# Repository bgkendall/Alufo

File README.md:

# Alufo

Small split keyboard using stacked one-layer aluminium core boards with an on-board CH552T controller.

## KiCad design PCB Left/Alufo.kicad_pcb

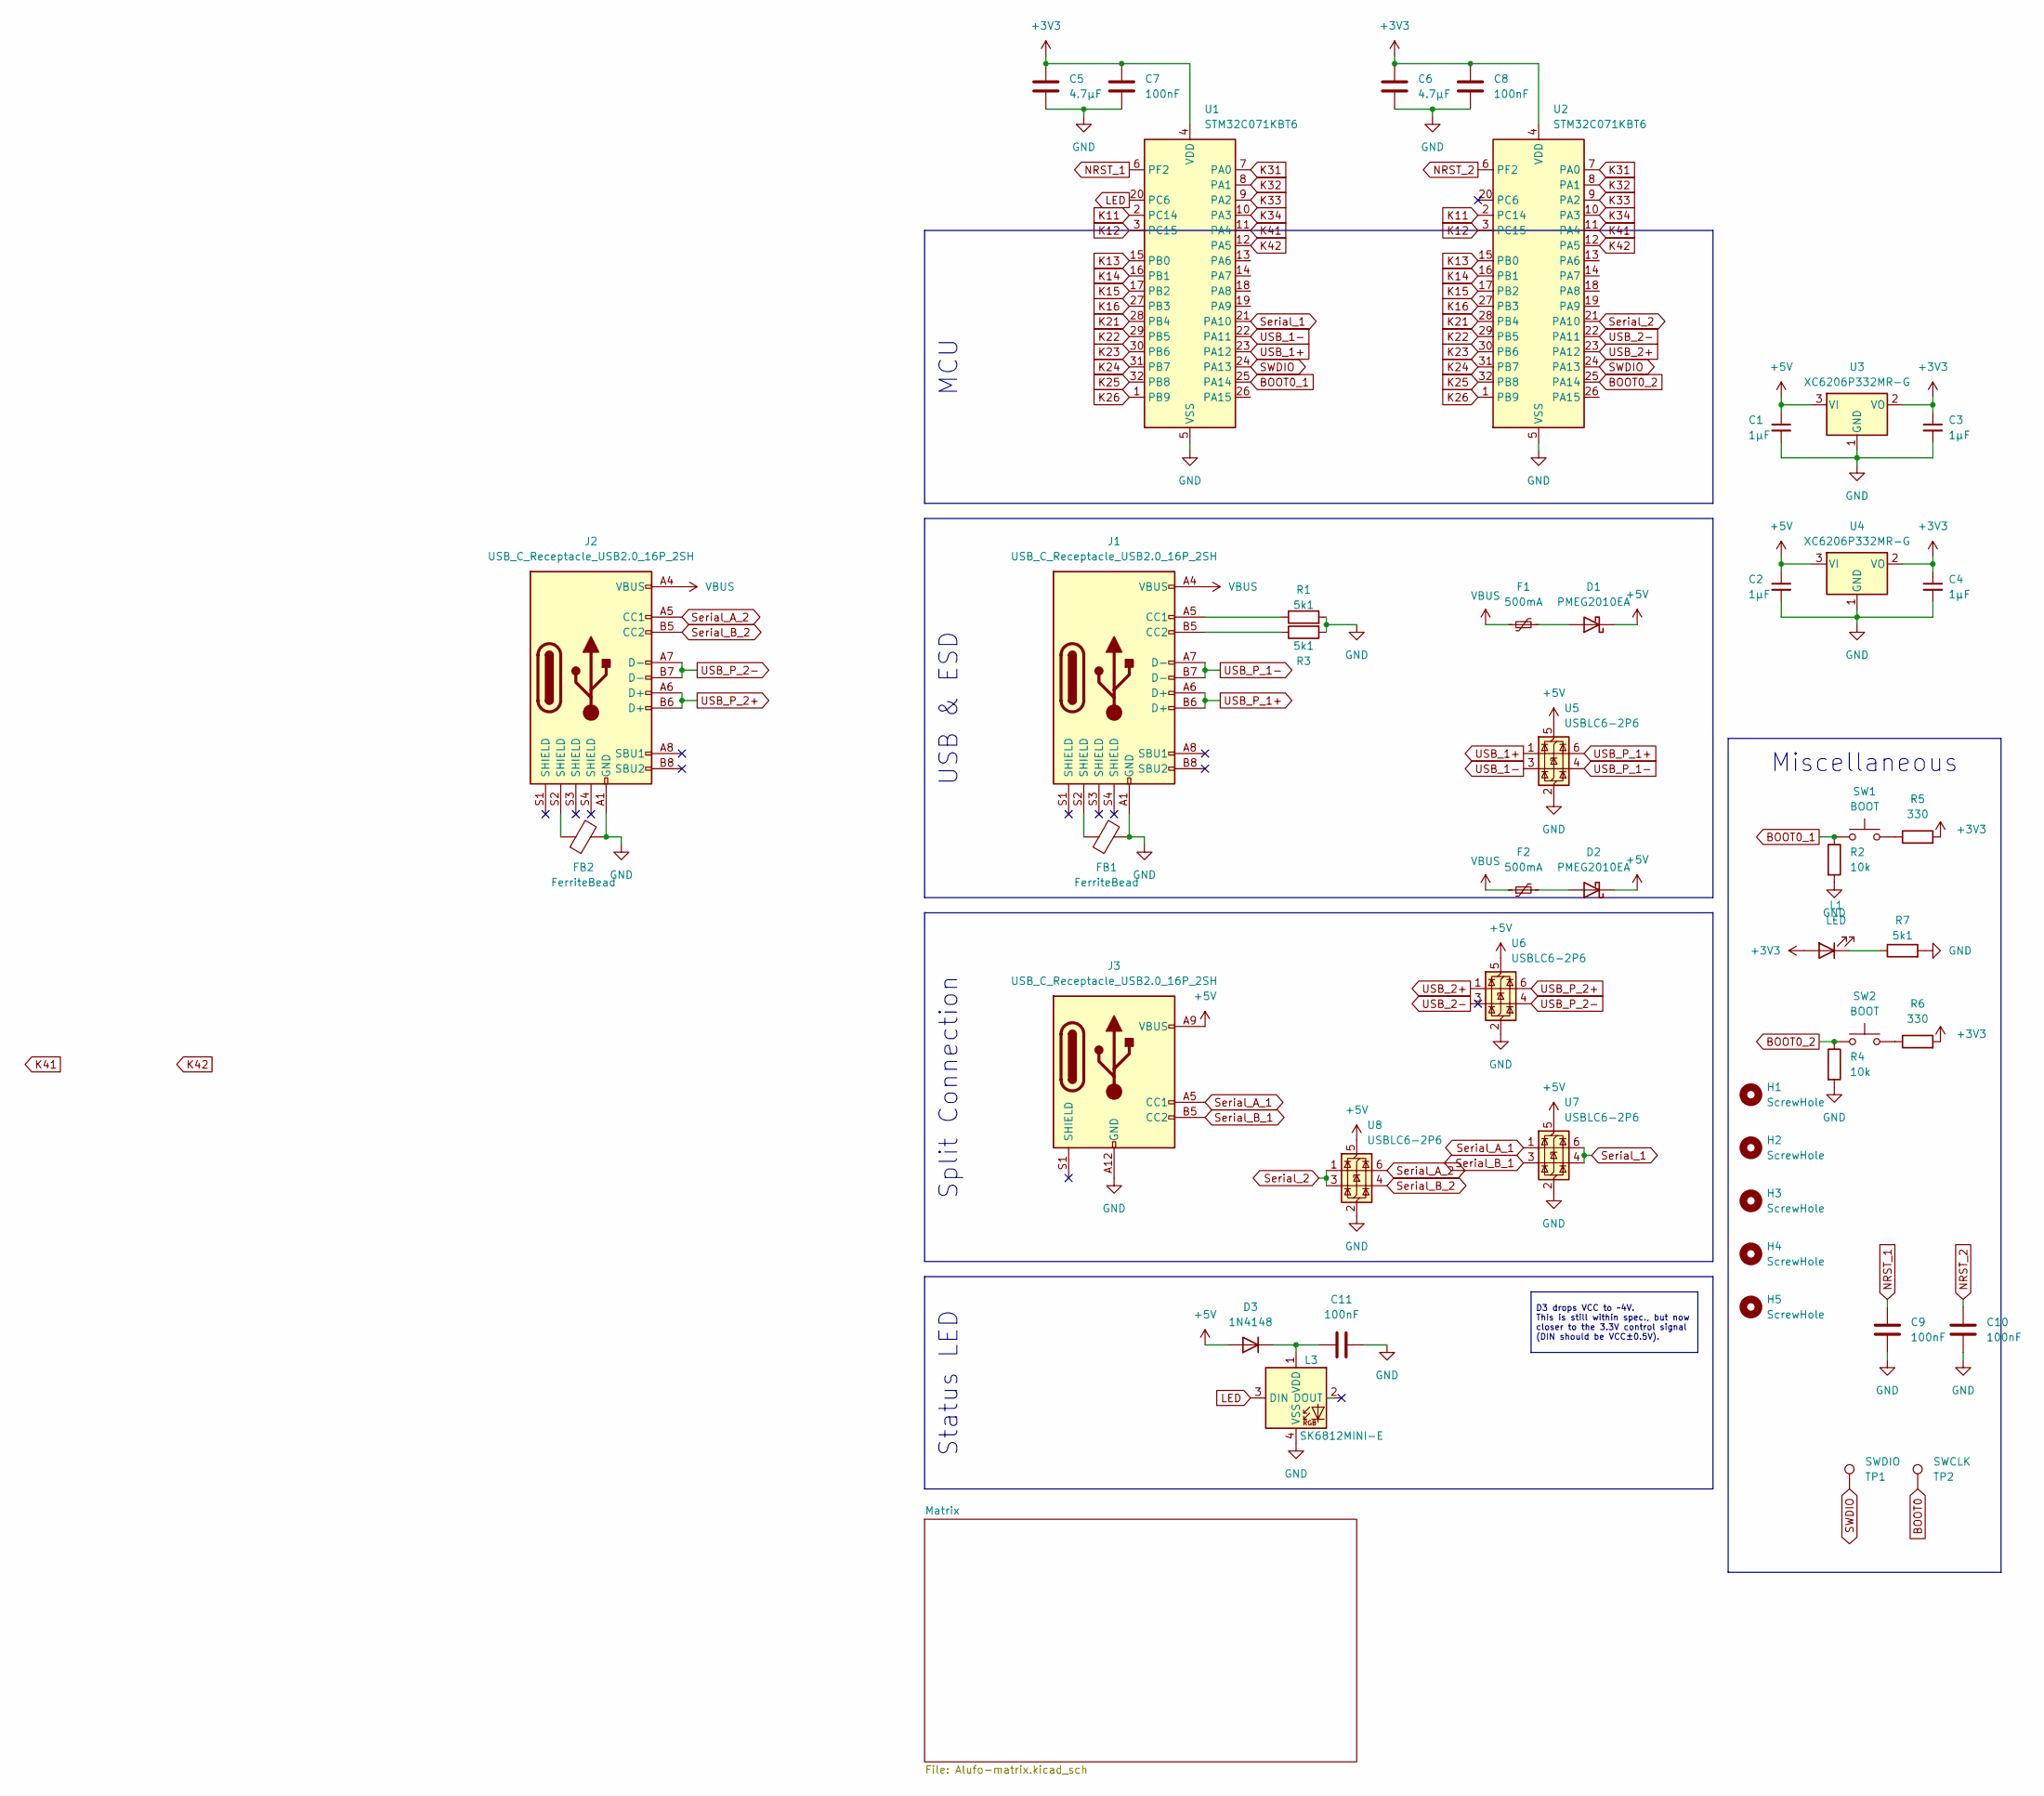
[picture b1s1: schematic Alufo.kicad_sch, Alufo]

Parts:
C1, C2, C3, C4: 1µF; C_0603_1608Metric; LCSC C52923
C5, C6: 4.7µF; C_0603_1608Metric
C7, C8, C9, C10: 100nF; C_0603_1608Metric
C11: 100nF; C_0603_1608Metric; LCSC C66501
D1, D2: PMEG2010EA; D_SOD-323; LCSC C193668
D3: 1N4148; D_SOD-123; LCSC C917030
F1, F2: 500mA; Fuse_0603_1608Metric; LCSC C210357
FB1, FB2: FerriteBead; L_0805_2012Metric; LCSC C20416196
H1, H2, H3, H4, H5: ScrewHole; MountingHole_2.2mm_M2
J1, J2: USB_C_Receptacle_USB2.0_16P_2SH; USB_C_Receptacle_HRO_TYPE-C-31-M-12; LCSC C165948
J3: USB_C_Receptacle_USB2.0_16P_2SH; USB_C_Receptacle_HRO_TYPE-C-31-M-17; LCSC C165948
L1: LED; LED_0805_2012Metric_Mod; LCSC C965818
L3: SK6812MINI-E; LED_6028R; LCSC C5149201
R1, R3, R7: 5k1; R_0603_1608Metric; LCSC C23186
R2, R4: 10k; R_0805_2012Metric
R5, R6: 330; R_0603_1608Metric
SW1, SW2: BOOT; SW_SPST_SKQG_WithStem; LCSC C115351
TP1: SWDIO; TestPoint_THTPad_D1.5mm_Drill0.7mm
TP2: SWCLK; TestPoint_THTPad_D1.5mm_Drill0.7mm
U1, U2: STM32C071KBT6; LQFP-32_7x7mm_P0.8mm
U3, U4: XC6206P332MR-G; SOT-23-3
U5, U6, U7, U8: USBLC6-2P6; SOT-23-6; LCSC C3647099

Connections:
+3V3: C3.1, C4.1, C5.1, C6.1, C7.1, C8.1, L1.2 (A), R5.2, R6.2, U1.4 (VDD), U2.4 (VDD), U3.2 (VO), U4.2 (VO)
+5V: C1.1, C2.1, D1.1 (K), D2.1 (K), D3.2 (A), J3.A9 (VBUS), J3.B9 (VBUS), U3.3 (VI), U4.3 (VI), U5.5 (VBUS), U6.5 (VBUS), U7.5 (VBUS), U8.5 (VBUS)
BOOT0: TP2.1
BOOT0_1: R2.1, SW1.1, U1.25 (PA14)
BOOT0_2: R4.1, SW2.1, U2.25 (PA14)
GND: C1.2, C2.2, C3.2, C4.2, C5.2, C6.2, C7.2, C8.2, C9.2, C10.2, C11.2, FB1.2, FB2.2, J1.A1 (GND), J1.A12 (GND), J1.B1 (GND), J1.B12 (GND), J2.A1 (GND), J2.A12 (GND), J2.B1 (GND), J2.B12 (GND), J3.A12 (GND), J3.B12 (GND), L3.4 (VSS), R1.2, R2.2, R3.2, R4.2, R7.2, U1.5 (VSS), U2.5 (VSS), U3.1 (GND), U4.1 (GND), U5.2 (GND), U6.2 (GND), U7.2 (GND), U8.2 (GND); also elsewhere on the board
K11: U1.2 (PC14), U2.2 (PC14); also elsewhere on the board
K12: U1.3 (PC15), U2.3 (PC15); also elsewhere on the board
K13: U1.15 (PB0), U2.15 (PB0); also elsewhere on the board
K14: U1.16 (PB1), U2.16 (PB1); also elsewhere on the board
K15: U1.17 (PB2), U2.17 (PB2); also elsewhere on the board
K16: U1.27 (PB3), U2.27 (PB3); also elsewhere on the board
K21: U1.28 (PB4), U2.28 (PB4); also elsewhere on the board
K22: U1.29 (PB5), U2.29 (PB5); also elsewhere on the board
K23: U1.30 (PB6), U2.30 (PB6); also elsewhere on the board
K24: U1.31 (PB7), U2.31 (PB7); also elsewhere on the board
K25: U1.32 (PB8), U2.32 (PB8); also elsewhere on the board
K26: U1.1 (PB9), U2.1 (PB9); also elsewhere on the board
K31: U1.7 (PA0), U2.7 (PA0); also elsewhere on the board
K32: U1.8 (PA1), U2.8 (PA1); also elsewhere on the board
K33: U1.9 (PA2), U2.9 (PA2); also elsewhere on the board
K34: U1.10 (PA3), U2.10 (PA3); also elsewhere on the board
K41: U1.11 (PA4), U2.11 (PA4); also elsewhere on the board
K42: U1.12 (PA5), U2.12 (PA5); also elsewhere on the board
LED: L3.3 (DIN), U1.20 (PC6)
NRST_1: C9.1, U1.6 (PF2)
NRST_2: C10.1, U2.6 (PF2)
unnamed: D1.2 (A), F1.2
unnamed: D2.2 (A), F2.2
unnamed: C11.1, D3.1 (K), L3.1 (VDD)
unnamed: FB1.1, J1.S2 (SHIELD)
unnamed: FB2.1, J2.S2 (SHIELD)
unnamed: J1.A5 (CC1), R1.1
unnamed: J1.B5 (CC2), R3.1
unnamed: L1.1 (K), R7.1
unnamed: R5.1, SW1.2
unnamed: R6.1, SW2.2
SWDIO: TP1.1, U1.24 (PA13), U2.24 (PA13)
Serial_1: U1.21 (PA10), U7.4 (I/O2), U7.6 (I/O1)
Serial_2: U2.21 (PA10), U8.1 (I/O1), U8.3 (I/O2)
Serial_A_1: J3.A5 (CC1), U7.1 (I/O1)
Serial_A_2: J2.A5 (CC1), U8.6 (I/O1)
Serial_B_1: J3.B5 (CC2), U7.3 (I/O2)
Serial_B_2: J2.B5 (CC2), U8.4 (I/O2)
USB_1+: U1.23 (PA12), U5.1 (I/O1)
USB_1-: U1.22 (PA11), U5.3 (I/O2)
USB_2+: U2.23 (PA12), U6.1 (I/O1)
USB_2-: U2.22 (PA11), U6.3 (I/O2)
USB_P_1+: J1.A6 (D+), J1.B6 (D+), U5.6 (I/O1)
USB_P_1-: J1.A7 (D-), J1.B7 (D-), U5.4 (I/O2)
USB_P_2+: J2.A6 (D+), J2.B6 (D+), U6.6 (I/O1)
USB_P_2-: J2.A7 (D-), J2.B7 (D-), U6.4 (I/O2)
VBUS: F1.1, F2.1, J1.A4 (VBUS), J1.A9 (VBUS), J1.B4 (VBUS), J1.B9 (VBUS), J2.A4 (VBUS), J2.A9 (VBUS), J2.B4 (VBUS), J2.B9 (VBUS)

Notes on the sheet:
MCU
Miscellaneous
Split Connection
USB & ESD
D3 drops VCC to ~4V. This is still within spec., but now closer to the 3.3V control signal (DIN should be VCC±0.5V).
Status LED

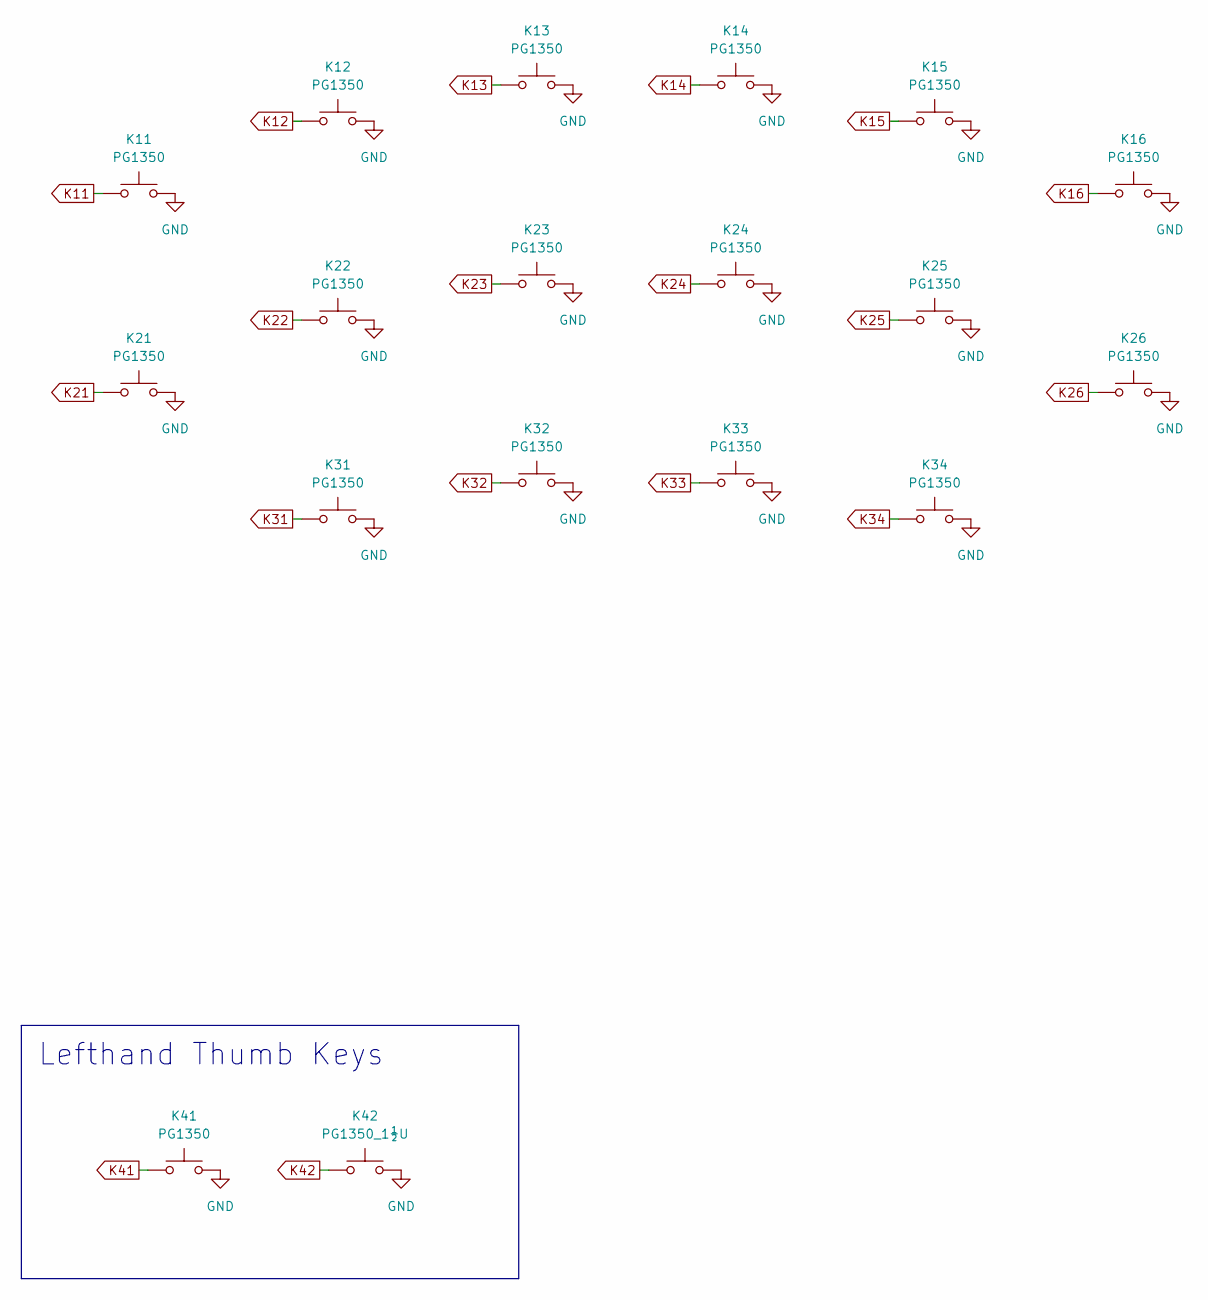
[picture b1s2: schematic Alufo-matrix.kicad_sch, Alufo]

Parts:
K11, K12, K13, K14, K15, K16, K21, K22, K23, K24, K25, K26, K31, K32, K33, K34, K41: PG1350; SW_Choc_v1_HS_CPG135001S30_1u_Reversible; LCSC C5333465
K42: PG1350_1½U; SW_Choc_v1_HS_CPG135001S30_1.5u_Reversible; LCSC C5333465

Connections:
GND: K11.1, K12.1, K13.1, K14.1, K15.1, K16.1, K21.1, K22.1, K23.1, K24.1, K25.1, K26.1, K31.1, K32.1, K33.1, K34.1, K41.1, K42.1; also elsewhere on the board
K11: K11.2; also elsewhere on the board
K12: K12.2; also elsewhere on the board
K13: K13.2; also elsewhere on the board
K14: K14.2; also elsewhere on the board
K15: K15.2; also elsewhere on the board
K16: K16.2; also elsewhere on the board
K21: K21.2; also elsewhere on the board
K22: K22.2; also elsewhere on the board
K23: K23.2; also elsewhere on the board
K24: K24.2; also elsewhere on the board
K25: K25.2; also elsewhere on the board
K26: K26.2; also elsewhere on the board
K31: K31.2; also elsewhere on the board
K32: K32.2; also elsewhere on the board
K33: K33.2; also elsewhere on the board
K34: K34.2; also elsewhere on the board
K41: K41.2; also elsewhere on the board
K42: K42.2; also elsewhere on the board

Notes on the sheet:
Lefthand Thumb Keys

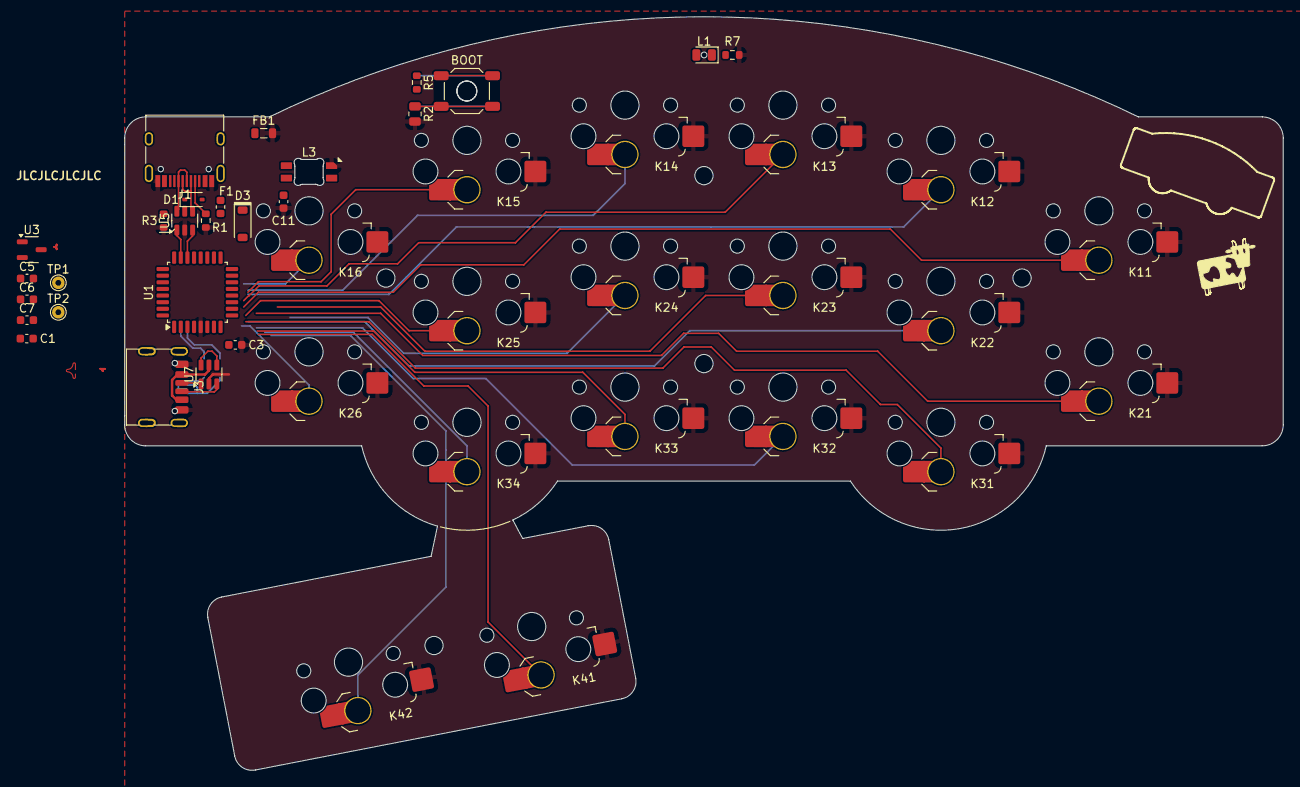
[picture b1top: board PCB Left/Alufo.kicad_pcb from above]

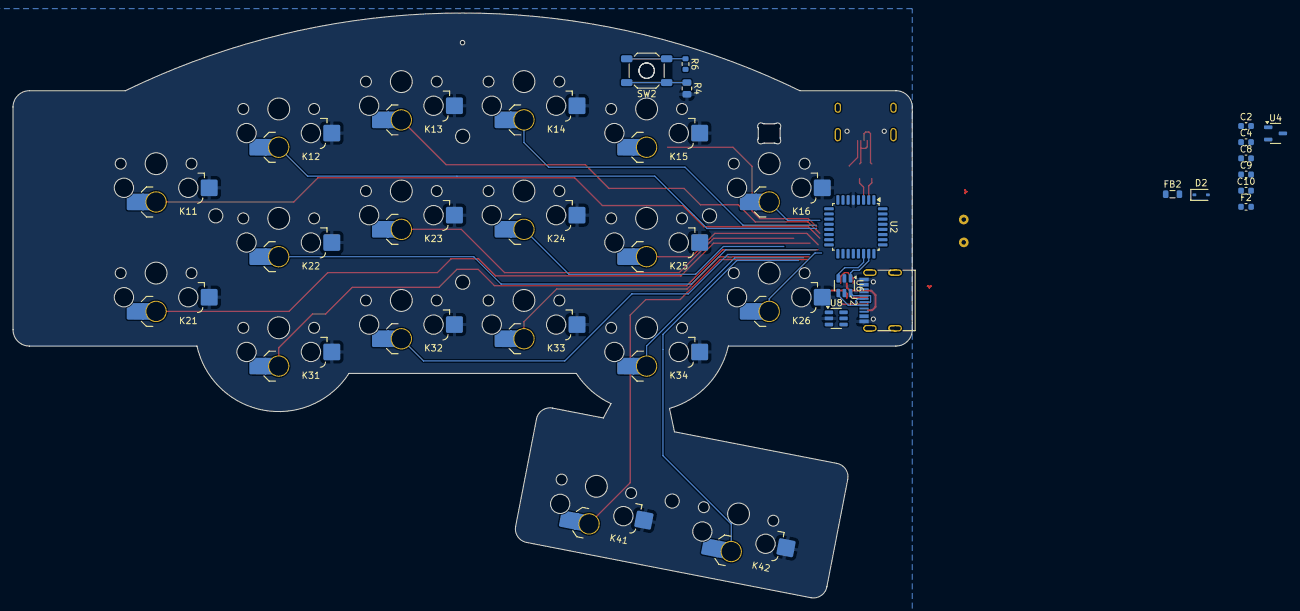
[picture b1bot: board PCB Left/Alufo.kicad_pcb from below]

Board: 2 copper layers, 139.7 x 90.9 mm, 65 parts (16 on the bottom side), 50 nets.

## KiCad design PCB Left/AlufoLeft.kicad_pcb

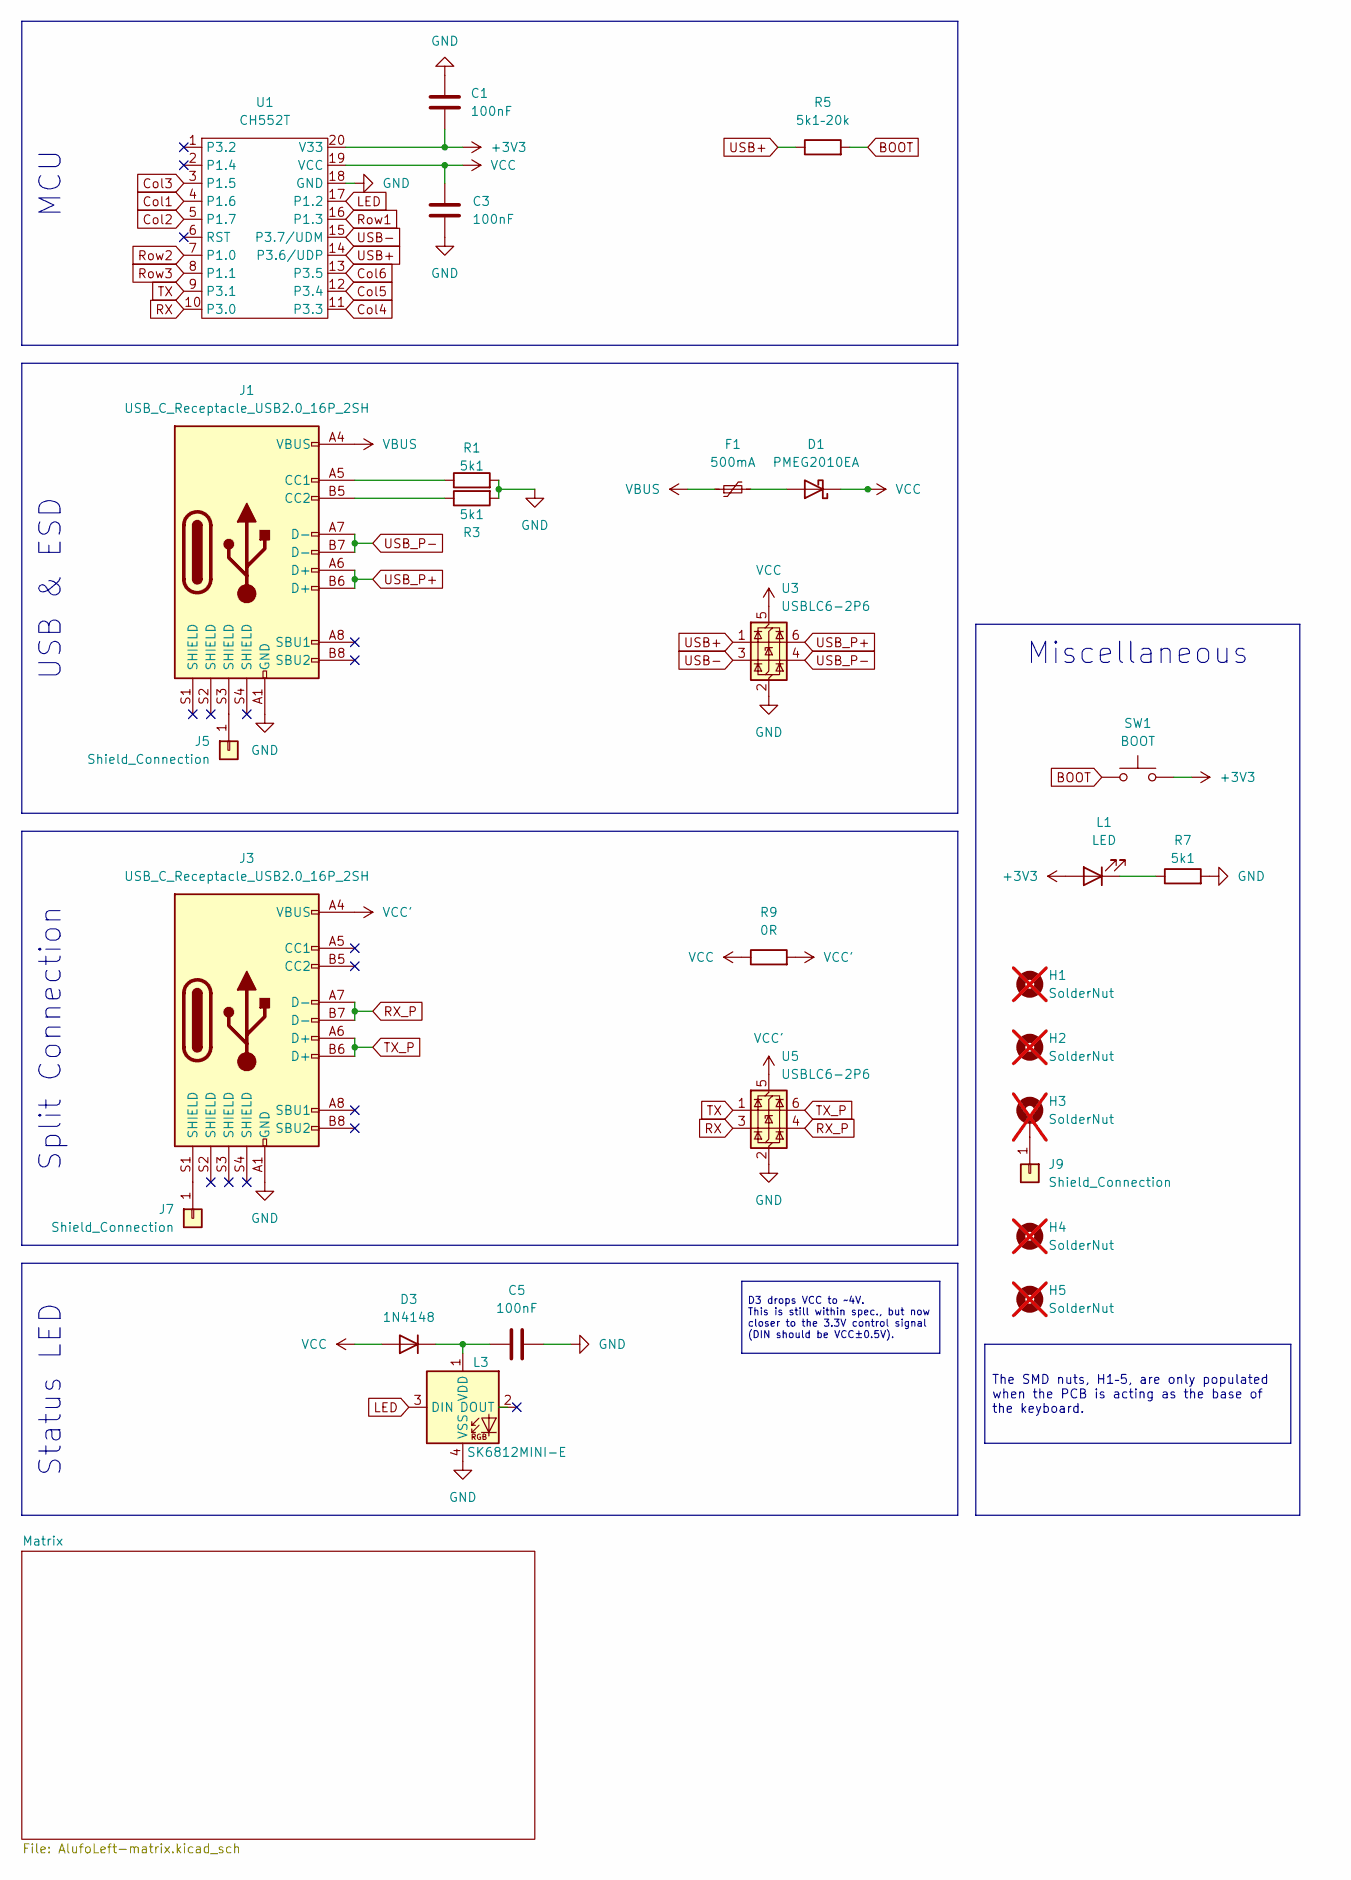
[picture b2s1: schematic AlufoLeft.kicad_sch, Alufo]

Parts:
C1, C3, C5: 100nF; C_0603_1608Metric; LCSC C66501
D1: PMEG2010EA; D_SOD-323; LCSC C193668
D3: 1N4148; D_SOD-123; LCSC C917030
F1: 500mA; Fuse_0603_1608Metric; LCSC C210357
H1, H2, H4, H5: SolderNut; MountingHole_2.2mm_M2_SMD_Solder_Nut; not fitted
H3: SolderNut; MountingHole_2.2mm_M2_SMD_Solder_Nut_Pad; not fitted
J1, J3: USB_C_Receptacle_USB2.0_16P_2SH; USB_C_Receptacle_GCT_USB4110; LCSC C2681552
J5, J7, J9: Shield_Connection; Shield_Connector
L1: LED; LED_0805_2012Metric_Mod; LCSC C965818
L3: SK6812MINI-E; LED_6028R; LCSC C5149201
R1, R3, R7: 5k1; R_0603_1608Metric; LCSC C23186
R5: 5k1–20k; R_0603_1608Metric; LCSC C25804
R9: 0R; R_0805_2012Metric; LCSC C2960848
SW1: BOOT; SW_SPST_SKQG_WithStem; LCSC C115351
U1: CH552T; TSSOP-20_4.4x6.5mm_P0.65mm; LCSC C111367
U3, U5: USBLC6-2P6; SOT-666_Mod; LCSC C3647099

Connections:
+3V3: C1.1, L1.2 (A), SW1.2, U1.20 (V33)
BOOT: R5.2, SW1.1
Col1: U1.4 (P1.6); also elsewhere on the board
Col2: U1.5 (P1.7); also elsewhere on the board
Col3: U1.3 (P1.5); also elsewhere on the board
Col4: U1.11 (P3.3); also elsewhere on the board
Col5: U1.12 (P3.4); also elsewhere on the board
Col6: U1.13 (P3.5); also elsewhere on the board
GND: C1.2, C3.2, C5.2, J1.A1 (GND), J1.A12 (GND), J1.B1 (GND), J1.B12 (GND), J3.A1 (GND), J3.A12 (GND), J3.B1 (GND), J3.B12 (GND), L3.4 (VSS), R1.2, R3.2, R7.2, U1.18 (GND), U3.2 (GND), U5.2 (GND)
LED: L3.3 (DIN), U1.17 (P1.2)
unnamed: D1.2 (A), F1.2
unnamed: C5.1, D3.1 (K), L3.1 (VDD)
unnamed: J1.A5 (CC1), R1.1
unnamed: J1.B5 (CC2), R3.1
unnamed: J1.S3 (SHIELD), J5.1
unnamed: J3.S1 (SHIELD), J7.1
unnamed: H3.1, J9.1
unnamed: L1.1 (K), R7.1
RX: U1.10 (P3.0), U5.3 (I/O2)
RX_P: J3.A7 (D-), J3.B7 (D-), U5.4 (I/O2)
Row1: U1.16 (P1.3); also elsewhere on the board
Row2: U1.7 (P1.0); also elsewhere on the board
Row3: U1.8 (P1.1); also elsewhere on the board
TX: U1.9 (P3.1), U5.1 (I/O1)
TX_P: J3.A6 (D+), J3.B6 (D+), U5.6 (I/O1)
USB+: R5.1, U1.14 (P3.6/UDP), U3.1 (I/O1)
USB-: U1.15 (P3.7/UDM), U3.3 (I/O2)
USB_P+: J1.A6 (D+), J1.B6 (D+), U3.6 (I/O1)
USB_P-: J1.A7 (D-), J1.B7 (D-), U3.4 (I/O2)
VBUS: F1.1, J1.A4 (VBUS), J1.A9 (VBUS), J1.B4 (VBUS), J1.B9 (VBUS)
VCC: C3.1, D1.1 (K), D3.2 (A), R9.1, U1.19 (VCC), U3.5 (VBUS)
VCC': J3.A4 (VBUS), J3.A9 (VBUS), J3.B4 (VBUS), J3.B9 (VBUS), R9.2, U5.5 (VBUS)

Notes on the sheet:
MCU
Miscellaneous
The SMD nuts, H1–5, are only populated when the PCB is acting as the base of the keyboard.
Split Connection
USB & ESD
D3 drops VCC to ~4V. This is still within spec., but now closer to the 3.3V control signal (DIN should be VCC±0.5V).
Status LED

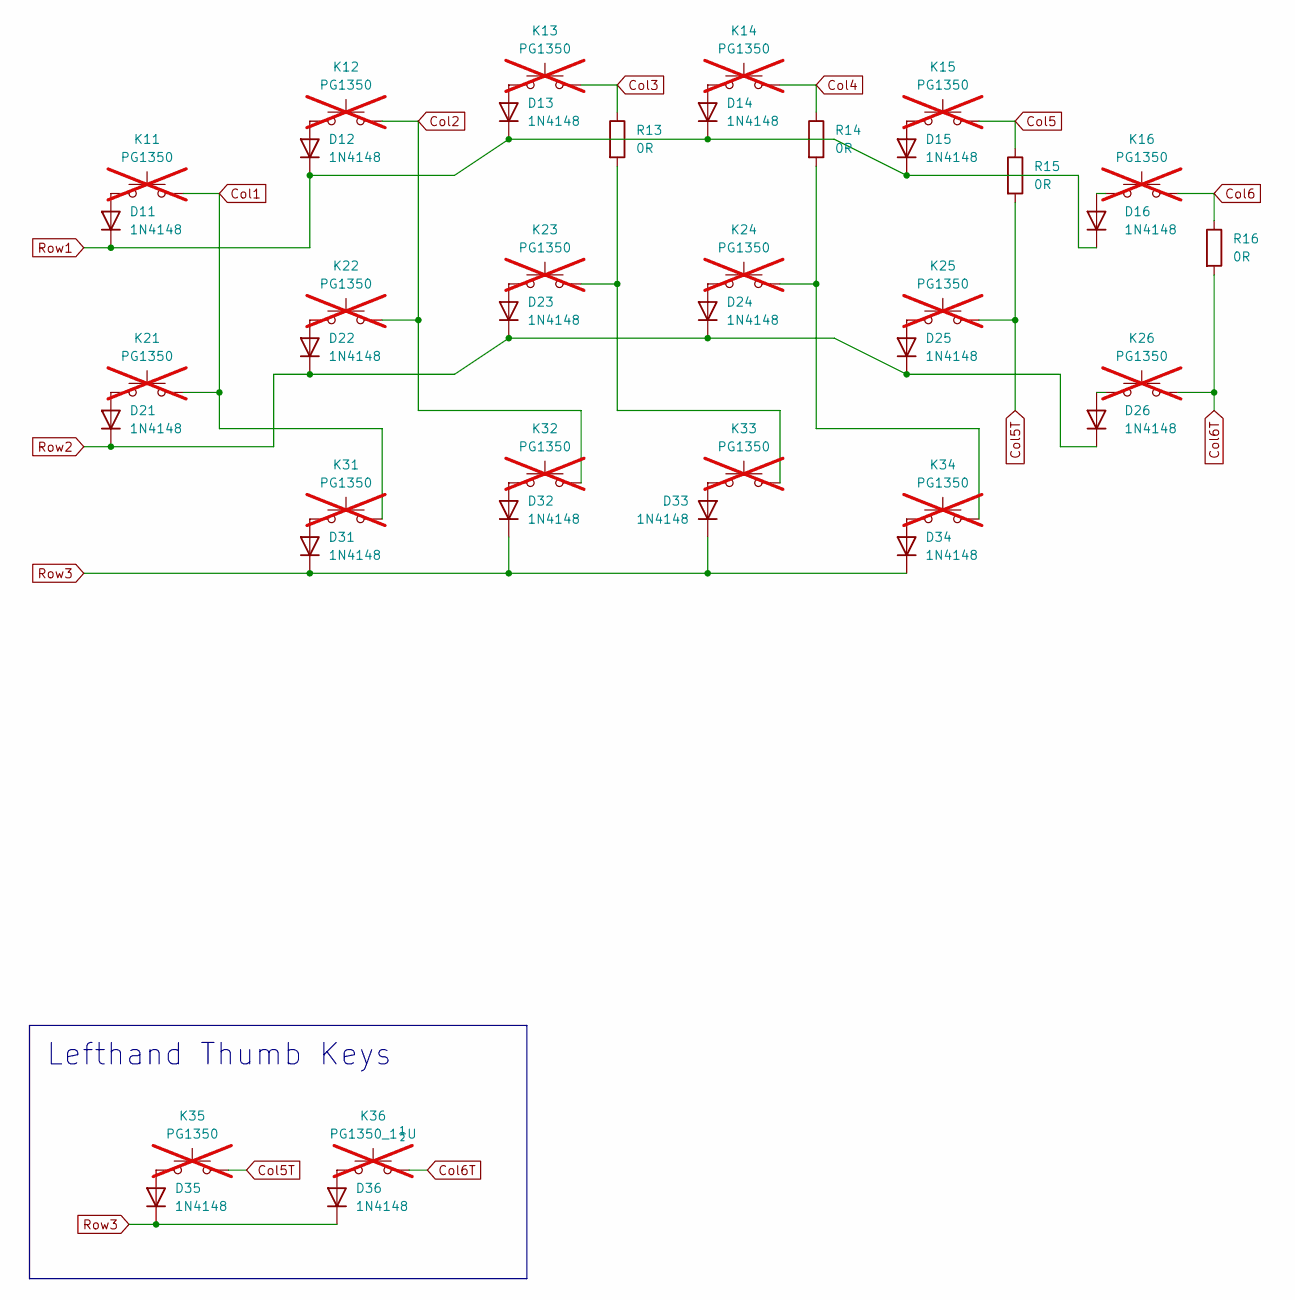
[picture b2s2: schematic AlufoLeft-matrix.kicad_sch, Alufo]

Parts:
D11, D12, D13, D14, D15, D16, D21, D22, D23, D24, D25, D26, D31, D32, D33, D34, D35, D36: 1N4148; D_SOD-123_Mod; LCSC C917030
K11, K12, K13, K14, K15, K16, K21, K22, K23, K24, K25, K26, K31, K32, K33, K34, K35: PG1350; SW_choc_v1_HS_CPG135001S30_1layer_1u; LCSC C5333465; not fitted
K36: PG1350_1½U; SW_choc_v1_HS_CPG135001S30_1layer_1.5u; LCSC C5333465; not fitted
R13, R14, R15, R16: 0R; R_2010_5025Metric; LCSC C2960848

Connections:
Col1: K11.1, K21.1, K31.1; also elsewhere on the board
Col2: K12.1, K22.1, K32.1; also elsewhere on the board
Col3: K13.1, R13.1; also elsewhere on the board
Col4: K14.1, R14.1; also elsewhere on the board
Col5: K15.1, R15.1; also elsewhere on the board
Col5T: K25.1, K35.1, R15.2
Col6: K16.1, R16.1; also elsewhere on the board
Col6T: K26.1, K36.1, R16.2
unnamed: D11.2 (A), K11.2
unnamed: D12.2 (A), K12.2
unnamed: D13.2 (A), K13.2
unnamed: D14.2 (A), K14.2
unnamed: D15.2 (A), K15.2
unnamed: D16.2 (A), K16.2
unnamed: D21.2 (A), K21.2
unnamed: D22.2 (A), K22.2
unnamed: D23.2 (A), K23.2
unnamed: D24.2 (A), K24.2
unnamed: D25.2 (A), K25.2
unnamed: D26.2 (A), K26.2
unnamed: D31.2 (A), K31.2
unnamed: D32.2 (A), K32.2
unnamed: D33.2 (A), K33.2
unnamed: D34.2 (A), K34.2
unnamed: D35.2 (A), K35.2
unnamed: D36.2 (A), K36.2
unnamed: K23.1, K33.1, R13.2
unnamed: K24.1, K34.1, R14.2
Row1: D11.1 (K), D12.1 (K), D13.1 (K), D14.1 (K), D15.1 (K), D16.1 (K); also elsewhere on the board
Row2: D21.1 (K), D22.1 (K), D23.1 (K), D24.1 (K), D25.1 (K), D26.1 (K); also elsewhere on the board
Row3: D31.1 (K), D32.1 (K), D33.1 (K), D34.1 (K), D35.1 (K), D36.1 (K); also elsewhere on the board

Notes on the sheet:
Lefthand Thumb Keys

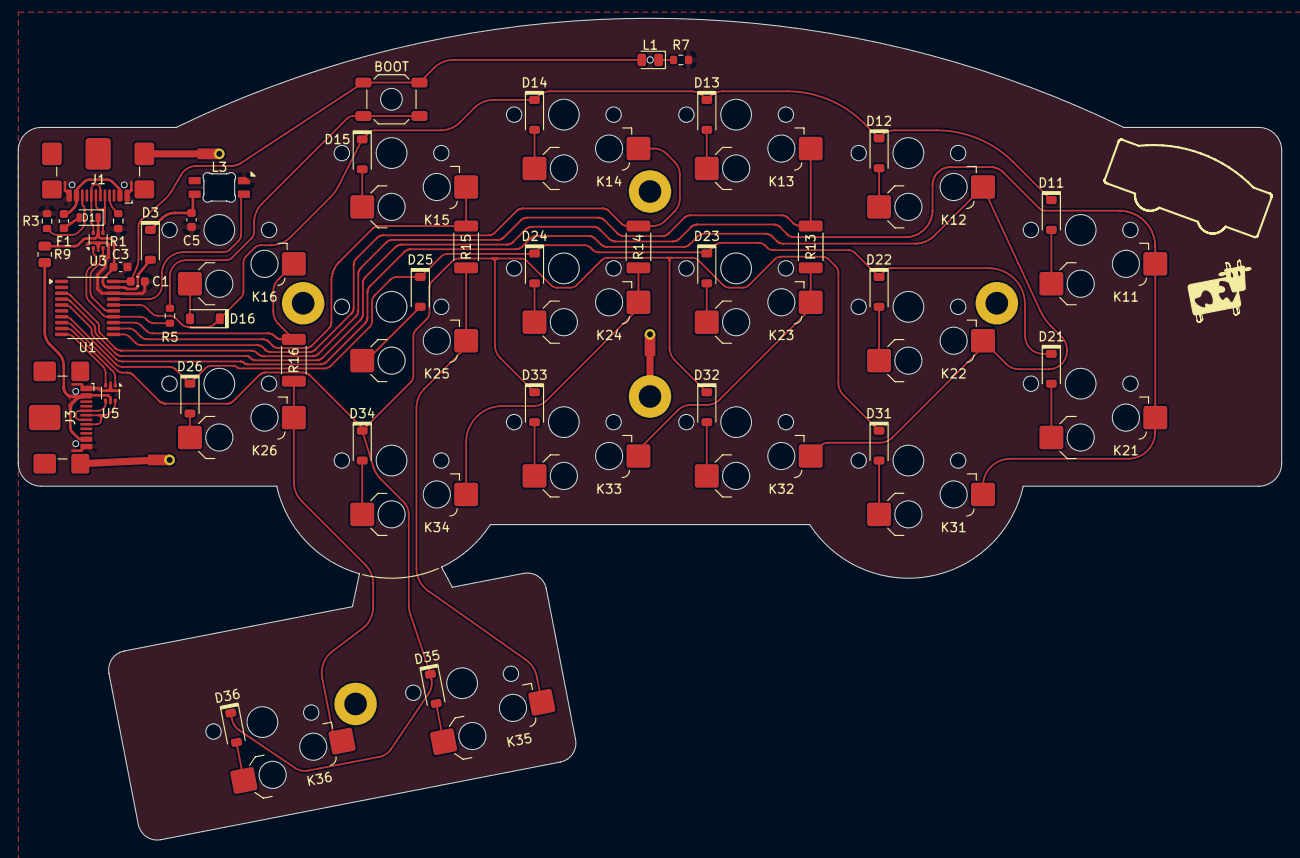
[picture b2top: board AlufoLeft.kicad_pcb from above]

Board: 2 copper layers, 139.7 x 90.9 mm, 67 parts (0 on the bottom side), 54 nets.

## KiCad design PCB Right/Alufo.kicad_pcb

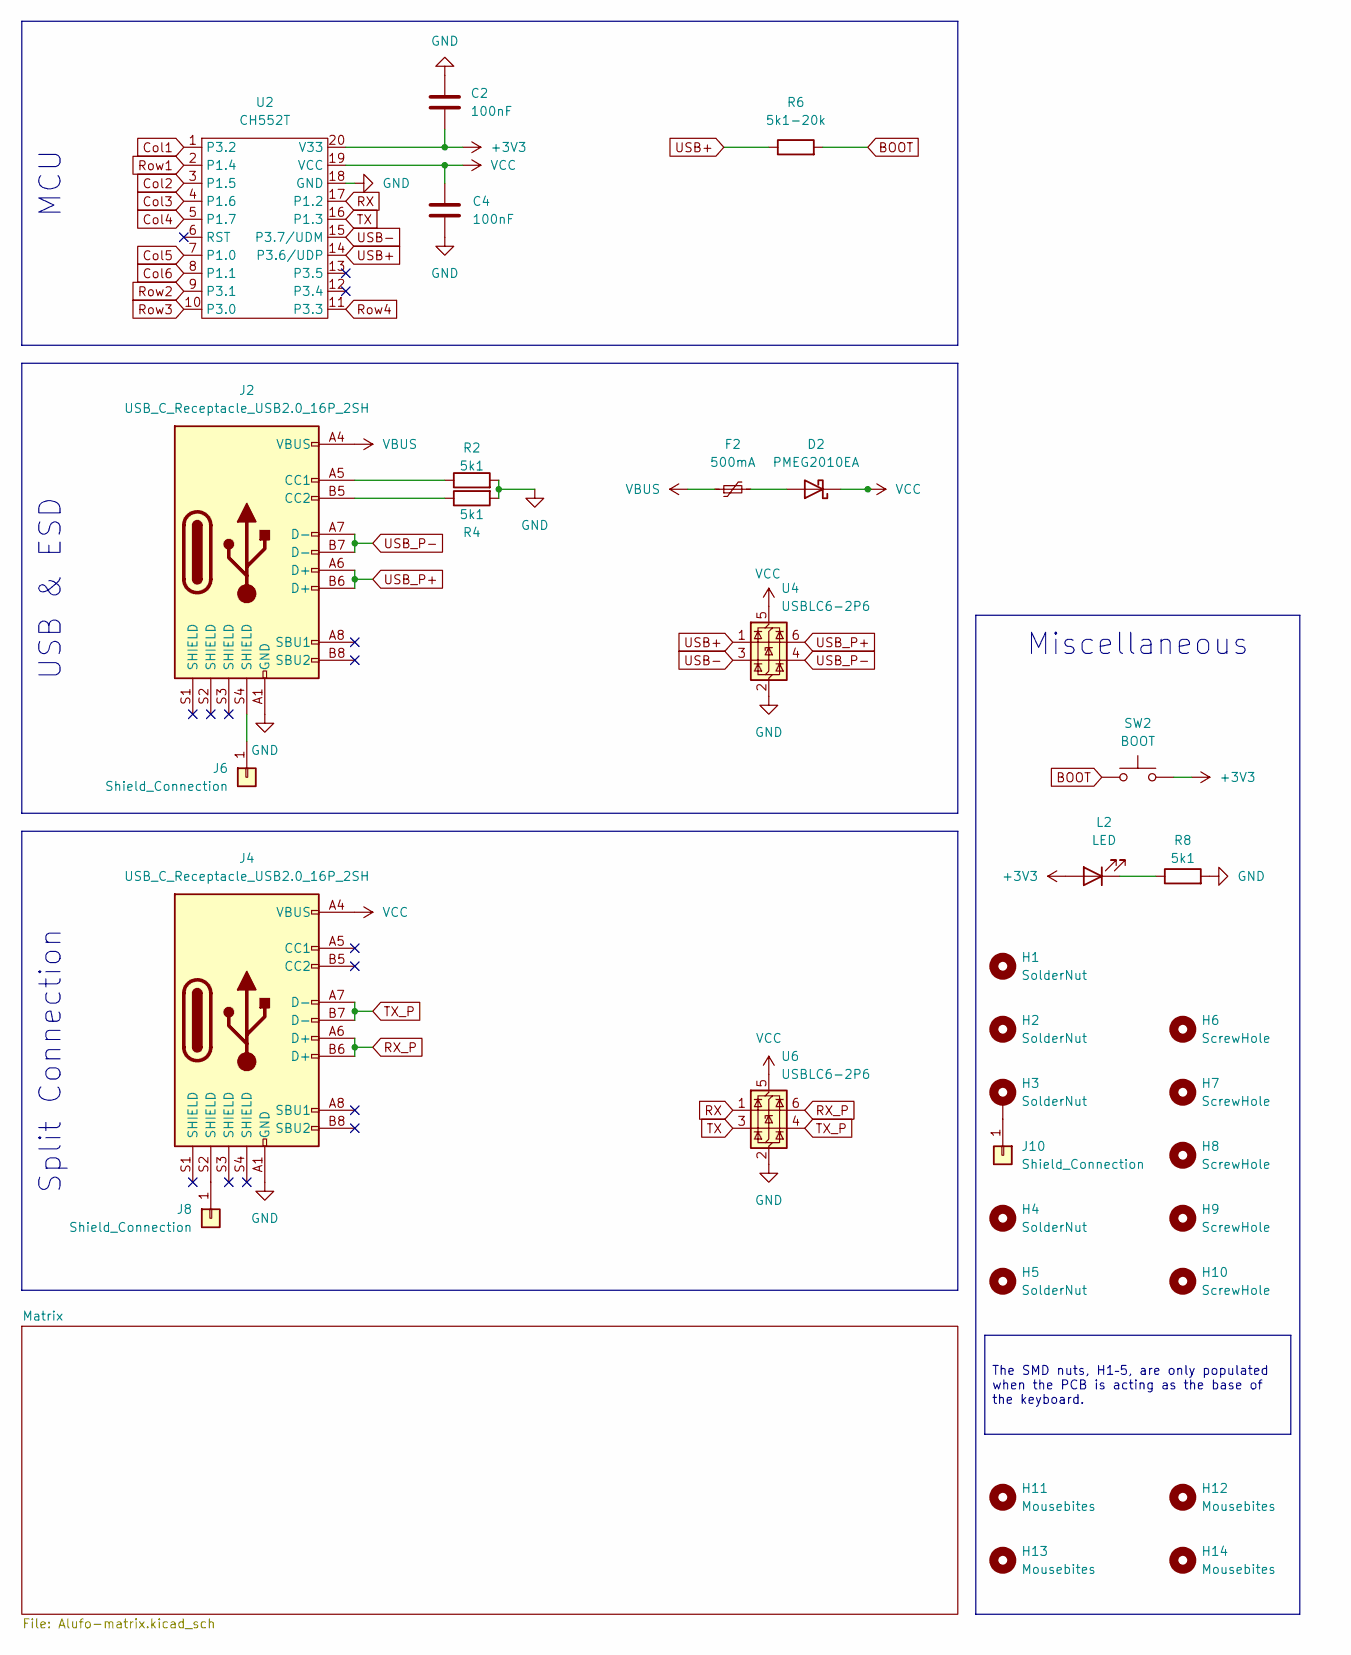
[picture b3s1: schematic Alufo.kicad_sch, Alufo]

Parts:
C2, C4: 100nF; C_0603_1608Metric; LCSC C66501
D2: PMEG2010EA; D_SOD-323; LCSC C193668
F2: 500mA; Fuse_0603_1608Metric; LCSC C210357
H1, H2, H4, H5: SolderNut; MountingHole_2.2mm_M2_SMD_Solder_Nut
H3: SolderNut; MountingHole_2.2mm_M2_SMD_Solder_Nut_Pad
H6, H7, H8, H9, H10: ScrewHole; MountingHole_2.2mm_M2
H11, H12, H13, H14: Mousebites
J2, J4: USB_C_Receptacle_USB2.0_16P_2SH; USB_C_Receptacle_GCT_USB4110; LCSC C2681552
J6, J8, J10: Shield_Connection; Shield_Connector
L2: LED; LED_0805_2012Metric_Mod; LCSC C965818
R2, R4, R8: 5k1; R_0603_1608Metric; LCSC C23186
R6: 5k1-20k; R_0603_1608Metric; LCSC C25804
SW2: BOOT; SW_SPST_SKQG_WithStem; LCSC C115351
U2: CH552T; TSSOP-20_4.4x6.5mm_P0.65mm; LCSC C111367
U4, U6: USBLC6-2P6; SOT-666_Mod; LCSC C3647099

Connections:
+3V3: C2.1, L2.2 (A), SW2.2, U2.20 (V33)
BOOT: R6.2, SW2.1
Col1: U2.1 (P3.2); also elsewhere on the board
Col2: U2.3 (P1.5); also elsewhere on the board
Col3: U2.4 (P1.6); also elsewhere on the board
Col4: U2.5 (P1.7); also elsewhere on the board
Col5: U2.7 (P1.0); also elsewhere on the board
Col6: U2.8 (P1.1); also elsewhere on the board
GND: C2.2, C4.2, J2.A1 (GND), J2.A12 (GND), J2.B1 (GND), J2.B12 (GND), J4.A1 (GND), J4.A12 (GND), J4.B1 (GND), J4.B12 (GND), R2.2, R4.2, R8.2, U2.18 (GND), U4.2 (GND), U6.2 (GND)
unnamed: D2.2 (A), F2.2
unnamed: J2.A5 (CC1), R2.1
unnamed: J2.B5 (CC2), R4.1
unnamed: J2.S4 (SHIELD), J6.1
unnamed: J4.S2 (SHIELD), J8.1
unnamed: H3.1, J10.1
unnamed: L2.1 (K), R8.1
RX: U2.17 (P1.2), U6.1 (I/O1)
RX_P: J4.A6 (D+), J4.B6 (D+), U6.6 (I/O1)
Row1: U2.2 (P1.4); also elsewhere on the board
Row2: U2.9 (P3.1); also elsewhere on the board
Row3: U2.10 (P3.0); also elsewhere on the board
Row4: U2.11 (P3.3); also elsewhere on the board
TX: U2.16 (P1.3), U6.3 (I/O2)
TX_P: J4.A7 (D-), J4.B7 (D-), U6.4 (I/O2)
USB+: R6.1, U2.14 (P3.6/UDP), U4.1 (I/O1)
USB-: U2.15 (P3.7/UDM), U4.3 (I/O2)
USB_P+: J2.A6 (D+), J2.B6 (D+), U4.6 (I/O1)
USB_P-: J2.A7 (D-), J2.B7 (D-), U4.4 (I/O2)
VBUS: F2.1, J2.A4 (VBUS), J2.A9 (VBUS), J2.B4 (VBUS), J2.B9 (VBUS)
VCC: C4.1, D2.1 (K), J4.A4 (VBUS), J4.A9 (VBUS), J4.B4 (VBUS), J4.B9 (VBUS), U2.19 (VCC), U4.5 (VBUS), U6.5 (VBUS)

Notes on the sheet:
MCU
Miscellaneous
Split Connection
USB & ESD
The SMD nuts, H1–5, are only populated when the PCB is acting as the base of the keyboard.
